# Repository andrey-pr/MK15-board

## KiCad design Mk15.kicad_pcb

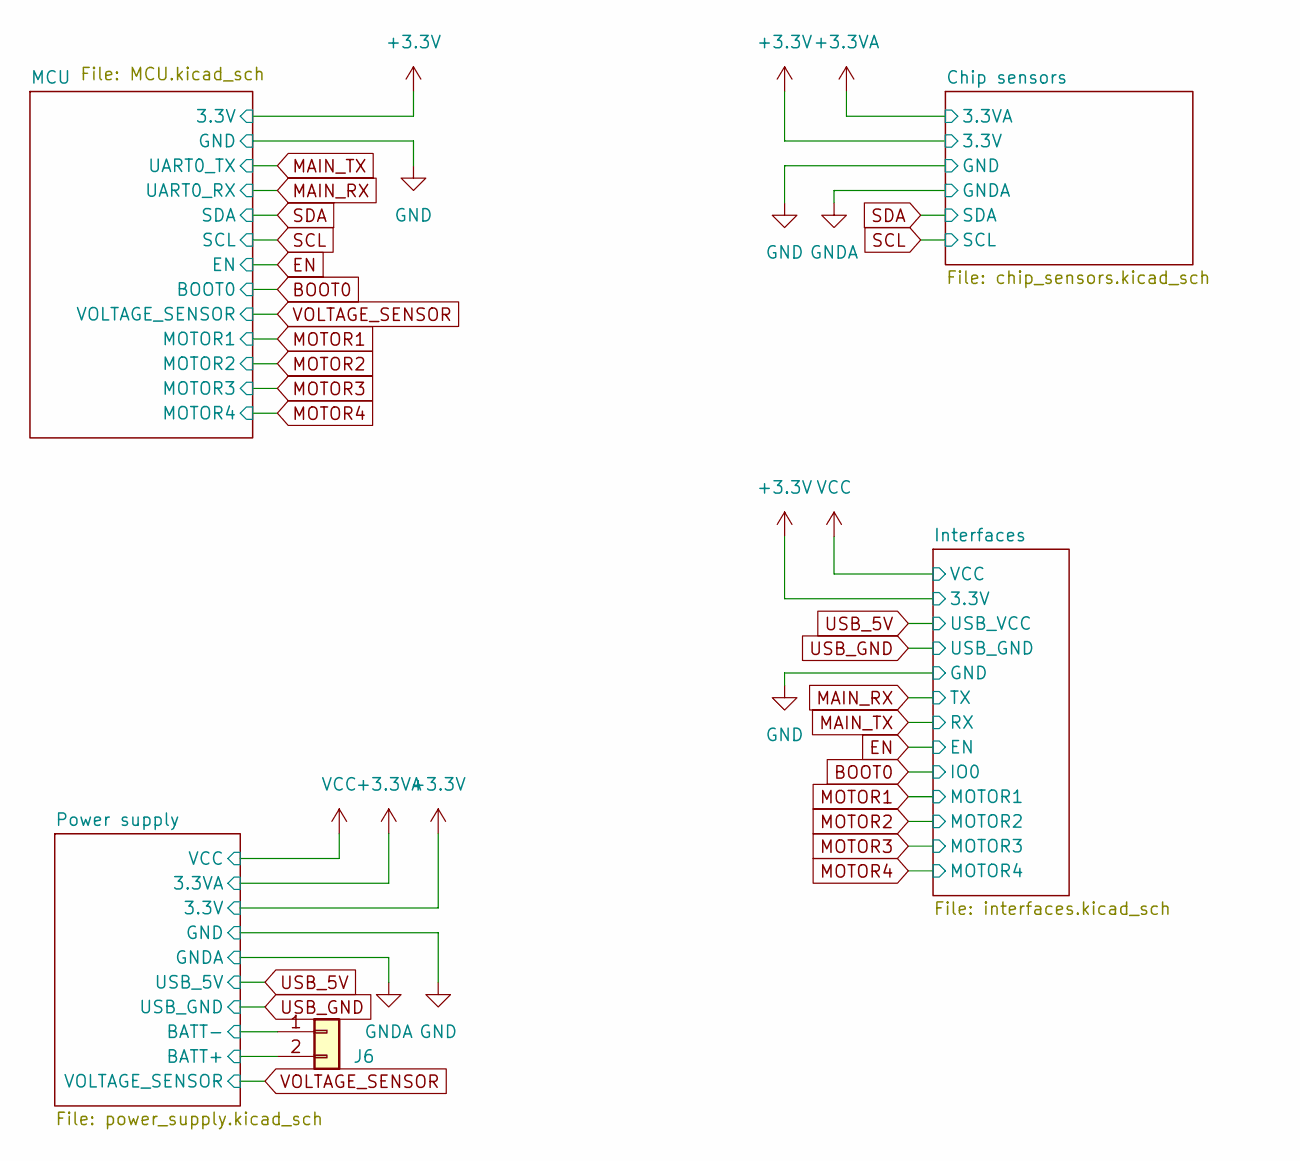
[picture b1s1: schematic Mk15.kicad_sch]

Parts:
J6: Conn_01x02; PinHeader_1x02_P2.54mm_Vertical

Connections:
-BATT: J6.1; also elsewhere on the board
VCC: J6.2; also elsewhere on the board

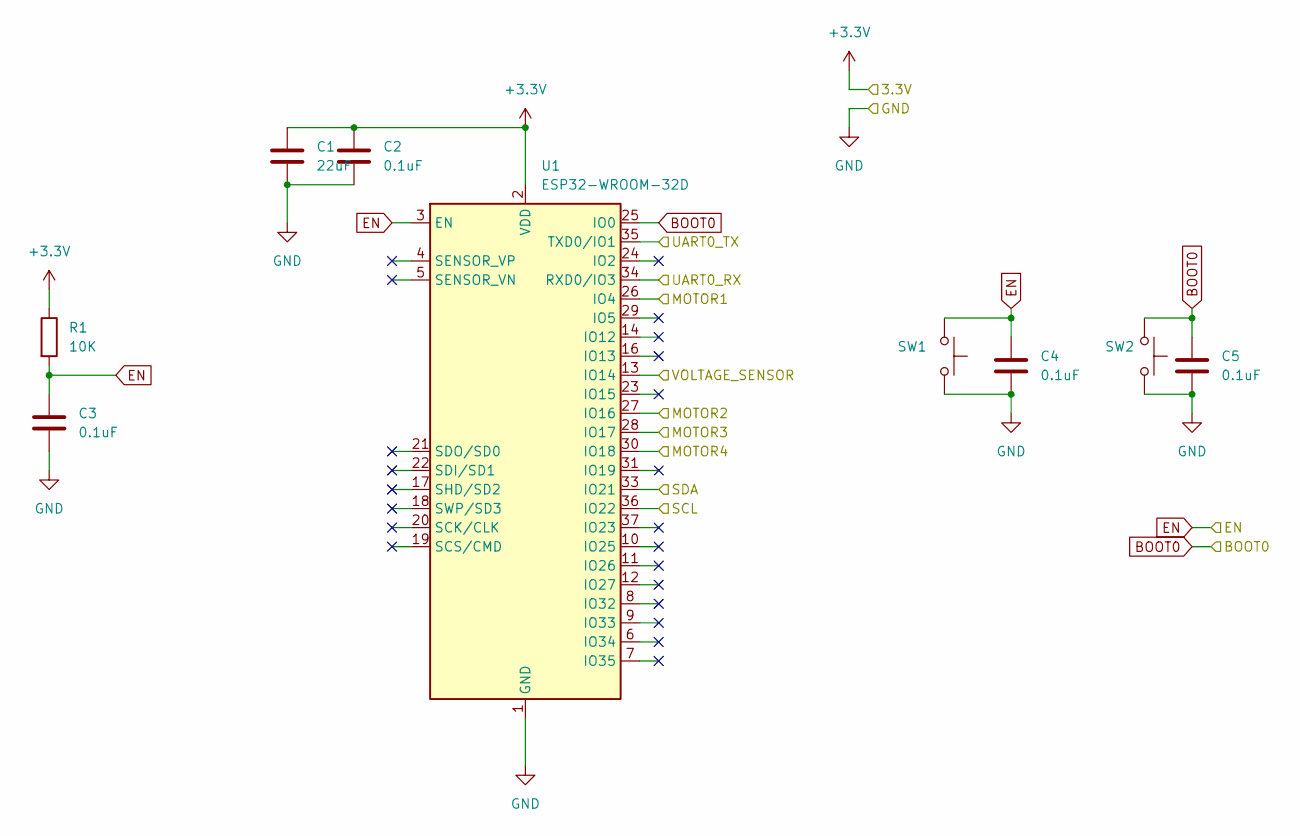
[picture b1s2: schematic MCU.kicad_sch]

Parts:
C1: 22uF; C_0805_2012Metric_Pad1.18x1.45mm_HandSolder
C2, C3, C4, C5: 0.1uF; C_0805_2012Metric_Pad1.18x1.45mm_HandSolder
R1: 10K; R_0805_2012Metric_Pad1.20x1.40mm_HandSolder
SW1, SW2: TS-1101-C-W; SW_SPST_CK_RS282G05A3
U1: ESP32-WROOM-32D; ESP32-WROOM-32

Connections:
+3.3V: C1.1, C2.1, R1.1, U1.2 (VDD); also elsewhere on the board
BOOT0: C5.1, SW2.1, U1.25 (IO0); also elsewhere on the board
EN: C3.1, C4.1, R1.2, SW1.1, U1.3 (EN); also elsewhere on the board
GND: C1.2, C2.2, C3.2, C4.2, C5.2, SW1.2, SW2.2, U1.1 (GND), U1.15 (GND), U1.38 (GND), U1.39 (GND); also elsewhere on the board
MAIN_RX: U1.34 (RXD0/IO3); also elsewhere on the board
MAIN_TX: U1.35 (TXD0/IO1); also elsewhere on the board
MOTOR1: U1.26 (IO4); also elsewhere on the board
MOTOR2: U1.27 (IO16); also elsewhere on the board
MOTOR3: U1.28 (IO17); also elsewhere on the board
MOTOR4: U1.30 (IO18); also elsewhere on the board
SCL: U1.36 (IO22); also elsewhere on the board
SDA: U1.33 (IO21); also elsewhere on the board
VOLTAGE_SENSOR: U1.13 (IO14); also elsewhere on the board

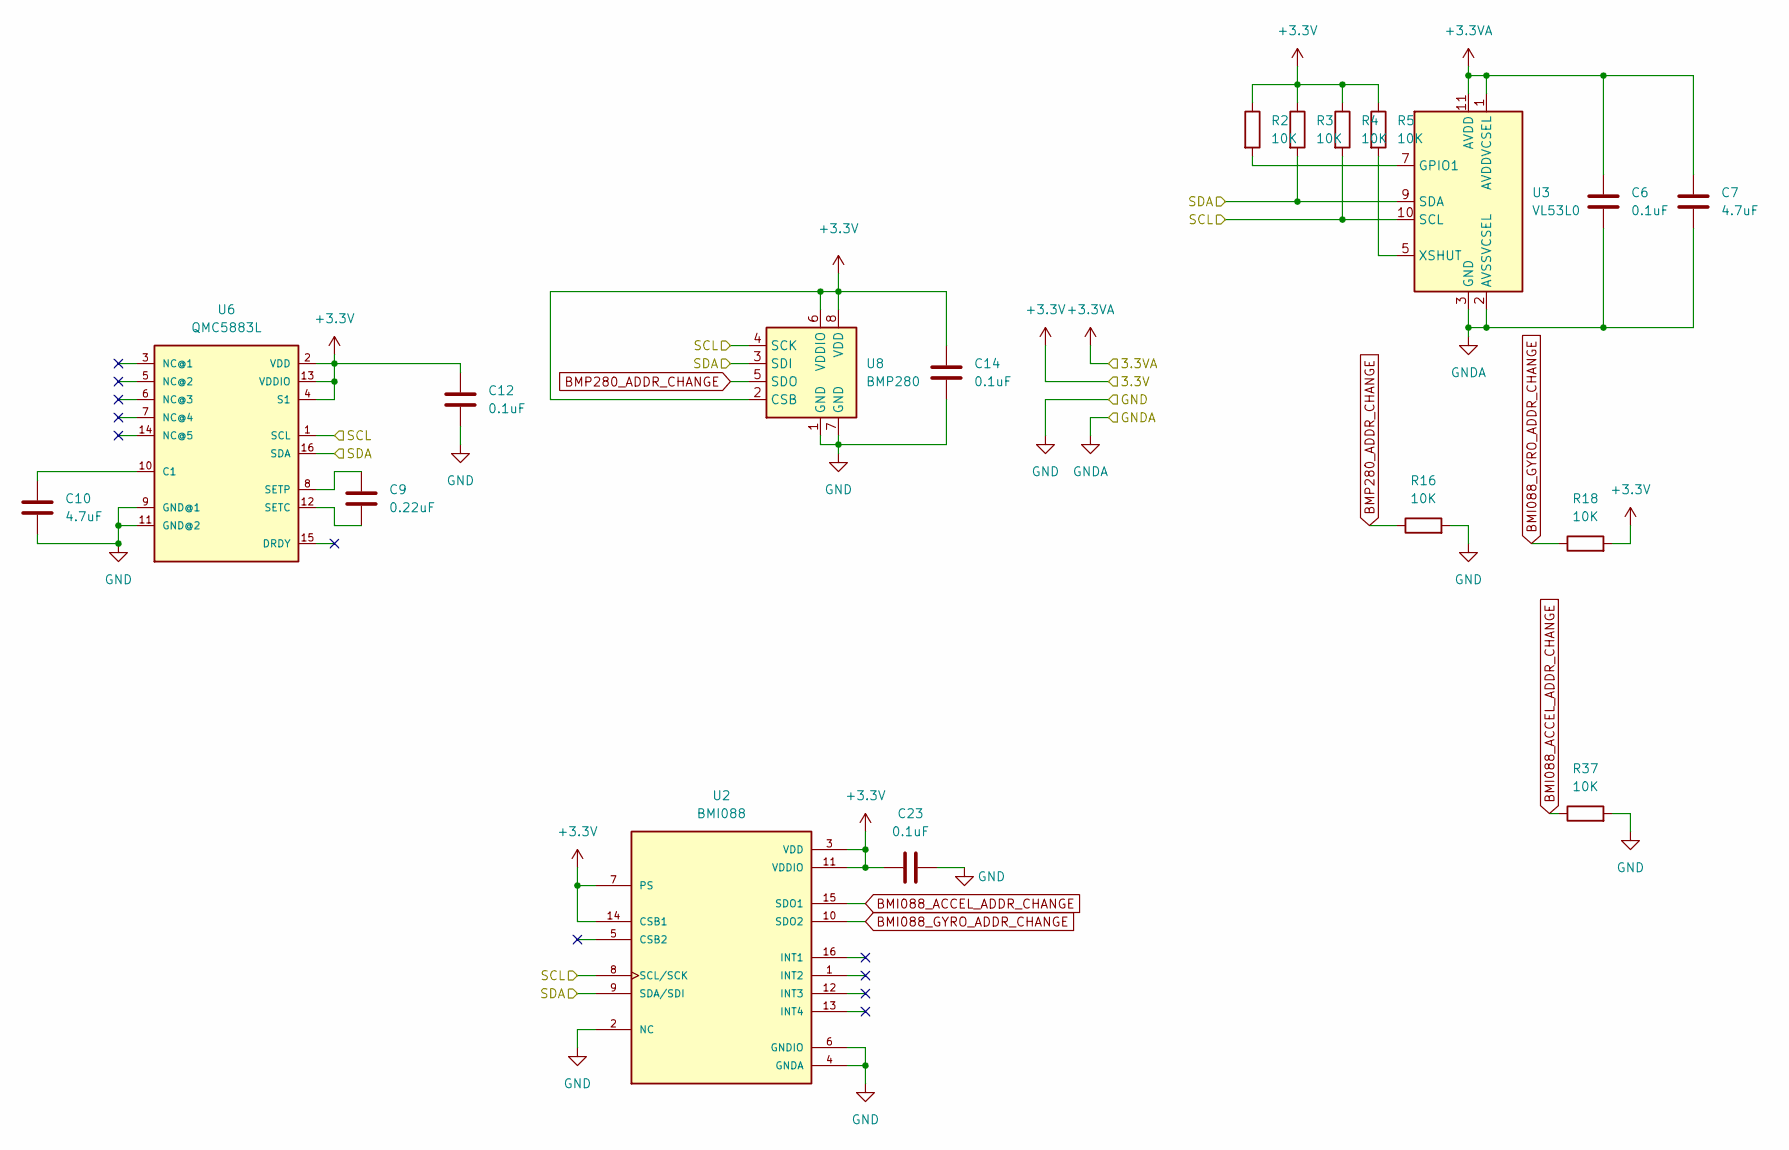
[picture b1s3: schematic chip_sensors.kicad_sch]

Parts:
C6, C12, C14, C23: 0.1uF; C_0805_2012Metric_Pad1.18x1.45mm_HandSolder
C7, C10: 4.7uF; C_0805_2012Metric_Pad1.18x1.45mm_HandSolder
C9: 0.22uF; C_0805_2012Metric_Pad1.18x1.45mm_HandSolder
R2, R3, R4, R5: 10K; R_0603_1608Metric_Pad0.98x0.95mm_HandSolder
R16, R18, R37: 10K; R_0805_2012Metric_Pad1.20x1.40mm_HandSolder
U2: BMI088; PQFN50P450X300X100-16N
U3: VL53L0; ST_VL53L0X
U6: QMC5883L; LPCC-16
U8: BMP280; Bosch_LGA-8_2x2.5mm_P0.65mm_ClockwisePinNumbering

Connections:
+3.3V: C12.1, C14.1, C23.2, R2.1, R3.1, R4.1, R5.1, R18.2, U2.3 (VDD), U2.7 (PS), U2.11 (VDDIO), U2.14 (CSB1), U6.2 (VDD), U6.4 (S1), U6.13 (VDDIO), U8.2 (CSB), U8.6 (VDDIO), U8.8 (VDD); also elsewhere on the board
+3.3VA: C6.1, C7.1, U3.1 (AVDDVCSEL), U3.11 (AVDD); also elsewhere on the board
BMI088_ACCEL_ADDR_CHANGE: R37.1, U2.15 (SDO1)
BMI088_GYRO_ADDR_CHANGE: R18.1, U2.10 (SDO2)
BMP280_ADDR_CHANGE: R16.1, U8.5 (SDO)
GND: C6.2, C7.2, C10.2, C12.2, C14.2, C23.1, R16.2, R37.2, U2.2 (NC), U2.4 (GNDA), U2.6 (GNDIO), U3.2 (AVSSVCSEL), U3.3 (GND), U3.4 (GND), U3.6 (GND), U3.12 (GND), U6.9 (GND@1), U6.11 (GND@2), U8.1 (GND), U8.7 (GND); also elsewhere on the board
unnamed: C9.1, U6.8 (SETP)
unnamed: C9.2, U6.12 (SETC)
unnamed: C10.1, U6.10 (C1)
unnamed: R2.2, U3.7 (GPIO1)
unnamed: R5.2, U3.5 (XSHUT)
SCL: R4.2, U2.8 (SCL/SCK), U3.10 (SCL), U6.1 (SCL), U8.4 (SCK); also elsewhere on the board
SDA: R3.2, U2.9 (SDA/SDI), U3.9 (SDA), U6.16 (SDA), U8.3 (SDI); also elsewhere on the board

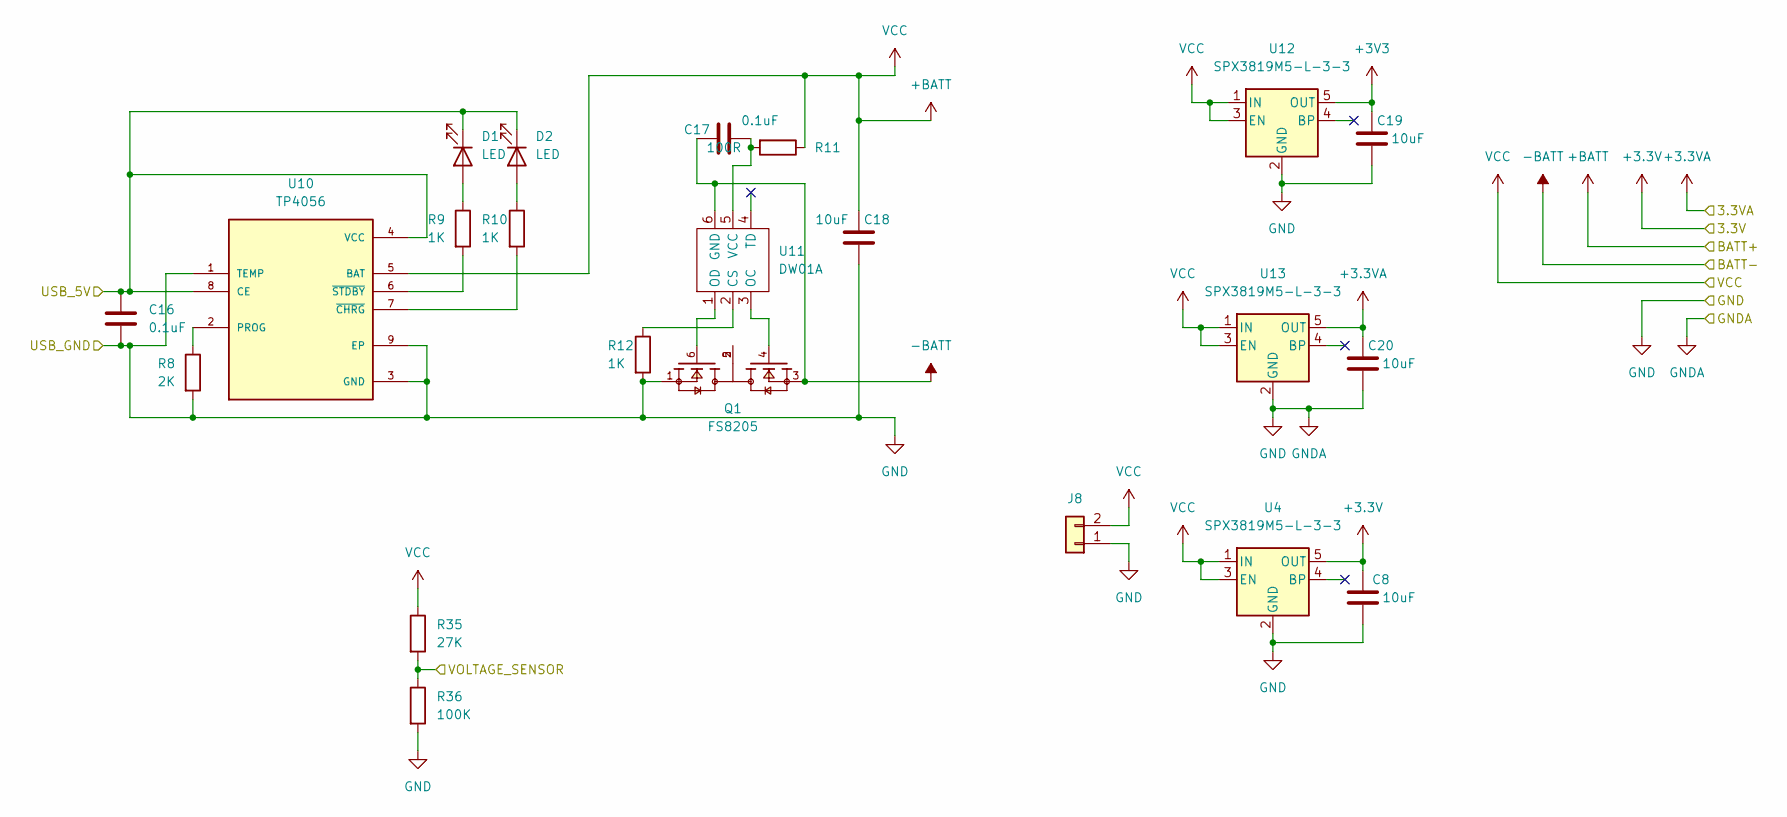
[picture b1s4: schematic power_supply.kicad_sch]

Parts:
C8, C18, C19, C20: 10uF; C_0805_2012Metric_Pad1.18x1.45mm_HandSolder
C16, C17: 0.1uF; C_0805_2012Metric_Pad1.18x1.45mm_HandSolder
D1, D2: LED; LED_0805_2012Metric_Pad1.15x1.40mm_HandSolder
J8: Conn_01x02; PinHeader_1x02_P2.54mm_Vertical
Q1: FS8205; SOT95P280X145-6N; PARTREV 1.9
R8: 2K; R_0805_2012Metric_Pad1.20x1.40mm_HandSolder
R9, R10, R12: 1K; R_0805_2012Metric_Pad1.20x1.40mm_HandSolder
R11: 100R; R_0805_2012Metric_Pad1.20x1.40mm_HandSolder
R35: 27K; R_0805_2012Metric_Pad1.20x1.40mm_HandSolder
R36: 100K; R_0805_2012Metric_Pad1.20x1.40mm_HandSolder
U4, U12, U13: SPX3819M5-L-3-3; SOT-23-5
U10: TP4056; SOP127P600X175-9N
U11: DW01A; SOT-23-6_Handsoldering

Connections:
+3.3V: C8.2, U4.5 (OUT); also elsewhere on the board
+3.3VA: C20.2, U13.5 (OUT); also elsewhere on the board
+3V3: C19.2, U12.5 (OUT); also elsewhere on the board
-BATT: C17.2, Q1.3, U11.6 (GND); also elsewhere on the board
GND: C8.1, C16.2, C18.1, C19.1, C20.1, J8.1, Q1.1, R8.2, R12.2, R36.2, U4.2 (GND), U10.1 (TEMP), U10.3 (GND), U10.9 (EP), U12.2 (GND), U13.2 (GND); also elsewhere on the board
unnamed: C17.1, R11.2, U11.5 (VCC)
unnamed: D1.2 (A), R9.1
unnamed: D2.2 (A), R10.1
unnamed: Q1.2, Q1.5
unnamed: Q1.4, U11.3 (OC)
unnamed: Q1.6, U11.1 (OD)
unnamed: R8.1, U10.2 (PROG)
unnamed: R9.2, U10.6 (~STDBY)
unnamed: R10.2, U10.7 (~CHRG)
unnamed: R12.1, U11.2 (CS)
USB_5V: C16.1, D1.1 (K), D2.1 (K), U10.4 (VCC), U10.8 (CE); also elsewhere on the board
VCC: C18.2, J8.2, R11.1, R35.1, U4.1 (IN), U4.3 (EN), U10.5 (BAT), U12.1 (IN), U12.3 (EN), U13.1 (IN), U13.3 (EN); also elsewhere on the board
VOLTAGE_SENSOR: R35.2, R36.1; also elsewhere on the board

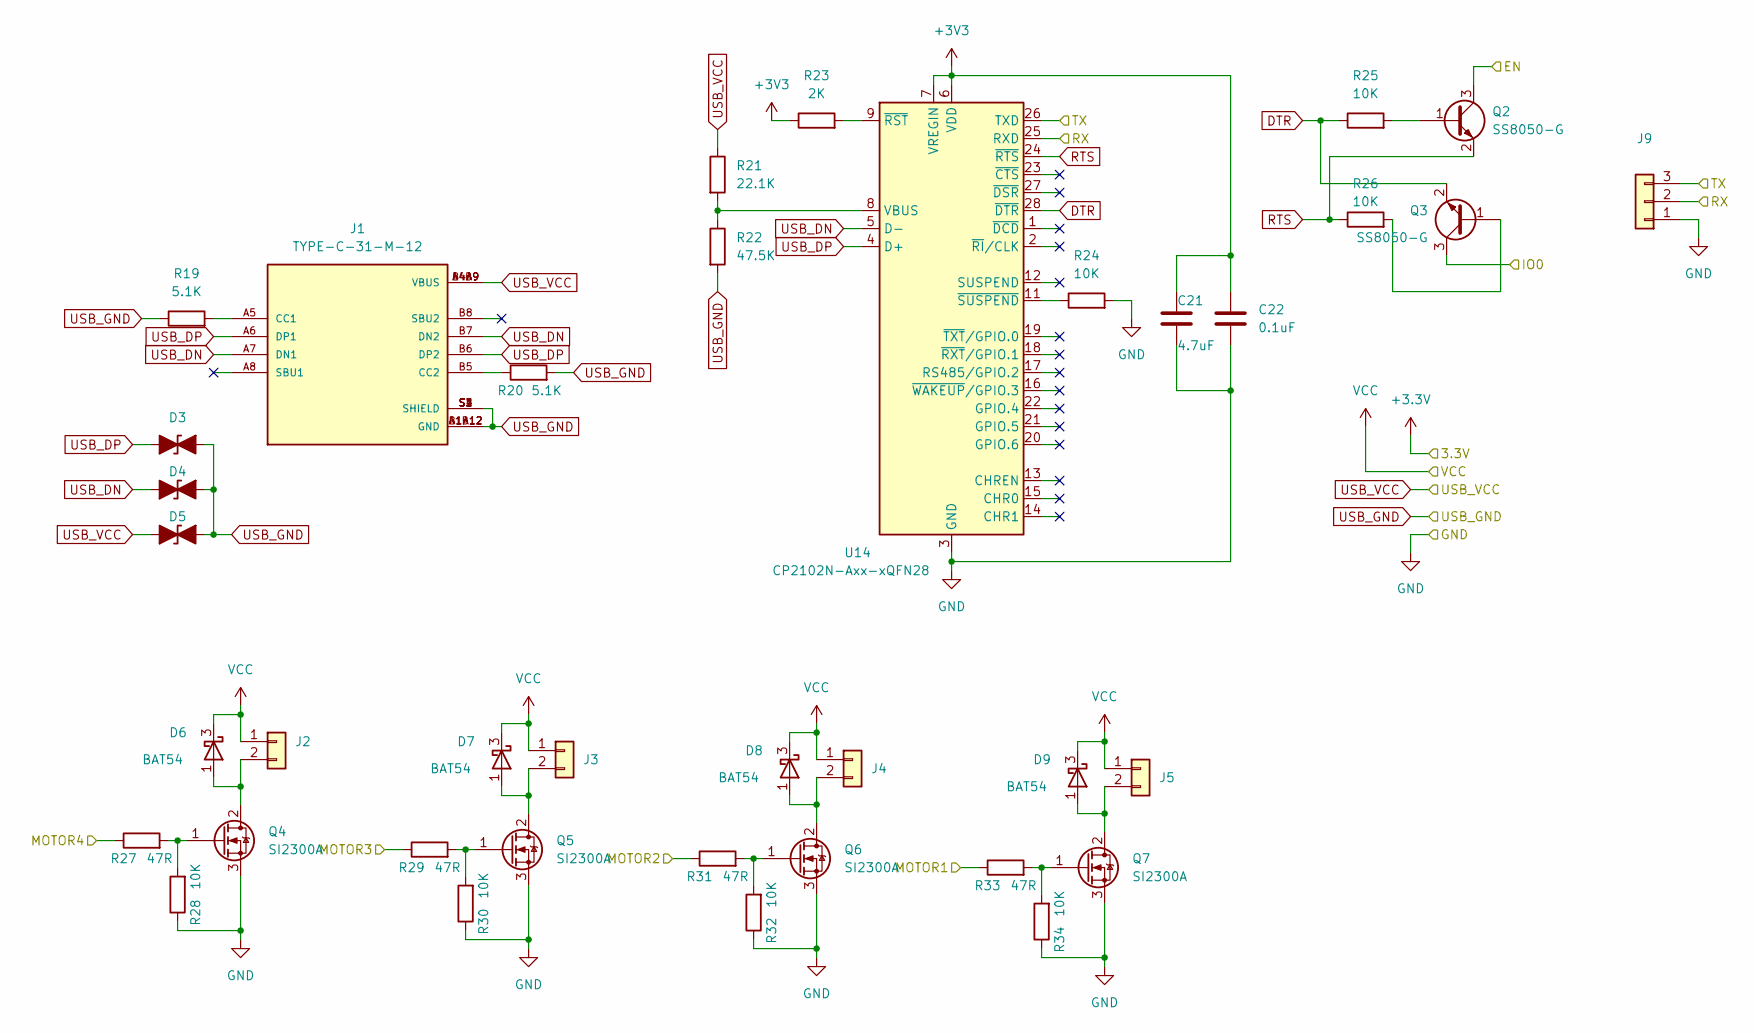
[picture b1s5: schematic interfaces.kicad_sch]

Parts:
C21: 4.7uF; C_0805_2012Metric_Pad1.18x1.45mm_HandSolder
C22: 0.1uF; C_0805_2012Metric_Pad1.18x1.45mm_HandSolder
D3, D4, D5: LRC LESD5D5.0CT1G; D_SOD-523
D6, D7, D8, D9: BAT54; SOT-323_SC-70
J1: TYPE-C-31-M-12; HRO_TYPE-C-31-M-12; PARTREV A
J2, J3, J4, J5: Conn_01x02; PinSocket_1x02_P2.54mm_Vertical
J9: Conn_01x03; PinHeader_1x03_P2.54mm_Vertical
Q2, Q3: SS8050-G; SOT-23
Q4, Q5, Q6, Q7: SI2300A; SOT-23
R19, R20: 5.1K; R_0603_1608Metric_Pad0.98x0.95mm_HandSolder
R21: 22.1K; R_0603_1608Metric_Pad0.98x0.95mm_HandSolder
R22: 47.5K; R_0603_1608Metric_Pad0.98x0.95mm_HandSolder
R23: 2K; R_0603_1608Metric_Pad0.98x0.95mm_HandSolder
R24: 10K; R_0603_1608Metric_Pad0.98x0.95mm_HandSolder
R25, R26, R28, R30, R32, R34: 10K; R_0805_2012Metric_Pad1.20x1.40mm_HandSolder
R27, R29, R31, R33: 47R; R_0805_2012Metric_Pad1.20x1.40mm_HandSolder
U14: CP2102N-Axx-xQFN28; QFN-28-1EP_5x5mm_P0.5mm_EP3.35x3.35mm

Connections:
+3V3: C21.1, C22.1, R23.1, U14.6 (VDD), U14.7 (VREGIN); also elsewhere on the board
BOOT0: Q3.3 (C); also elsewhere on the board
DTR: Q3.2 (E), R25.1, U14.28 (~DTR)
EN: Q2.3 (C); also elsewhere on the board
GND: C21.2, C22.2, D3.2 (A2), D4.2 (A2), D5.2 (A2), J1.A1B12 (GND), J1.B1A12 (GND), J1.S1 (SHIELD), J1.S2 (SHIELD), J1.S3 (SHIELD), J1.S4 (SHIELD), J9.1, Q4.3 (S), Q5.3 (S), Q6.3 (S), Q7.3 (S), R19.1, R20.2, R22.2, R24.2, R28.1, R30.1, R32.1, R34.1, U14.3 (GND), U14.29 (GND); also elsewhere on the board
MAIN_RX: J9.3, U14.26 (TXD); also elsewhere on the board
MAIN_TX: J9.2, U14.25 (RXD); also elsewhere on the board
MOTOR1: R33.1; also elsewhere on the board
MOTOR2: R31.1; also elsewhere on the board
MOTOR3: R29.1; also elsewhere on the board
MOTOR4: R27.1; also elsewhere on the board
unnamed: D6.1 (A), J2.2, Q4.2 (D)
unnamed: D7.1 (A), J3.2, Q5.2 (D)
unnamed: D8.1 (A), J4.2, Q6.2 (D)
unnamed: D9.1 (A), J5.2, Q7.2 (D)
unnamed: J1.A5 (CC1), R19.2
unnamed: J1.B5 (CC2), R20.1
unnamed: Q2.1 (B), R25.2
unnamed: Q3.1 (B), R26.2
unnamed: Q4.1 (G), R27.2, R28.2
unnamed: Q5.1 (G), R29.2, R30.2
unnamed: Q6.1 (G), R31.2, R32.2
unnamed: Q7.1 (G), R33.2, R34.2
unnamed: R21.2, R22.1, U14.8 (VBUS)
unnamed: R23.2, U14.9 (~RST)
unnamed: R24.1, U14.11 (~SUSPEND)
RTS: Q2.2 (E), R26.1, U14.24 (~RTS)
USB_5V: D5.1 (A1), J1.A4B9 (VBUS), J1.B4A9 (VBUS), R21.1; also elsewhere on the board
USB_DN: D4.1 (A1), J1.A7 (DN1), J1.B7 (DN2), U14.5 (D-)
USB_DP: D3.1 (A1), J1.A6 (DP1), J1.B6 (DP2), U14.4 (D+)
VCC: D6.3 (K), D7.3 (K), D8.3 (K), D9.3 (K), J2.1, J3.1, J4.1, J5.1; also elsewhere on the board

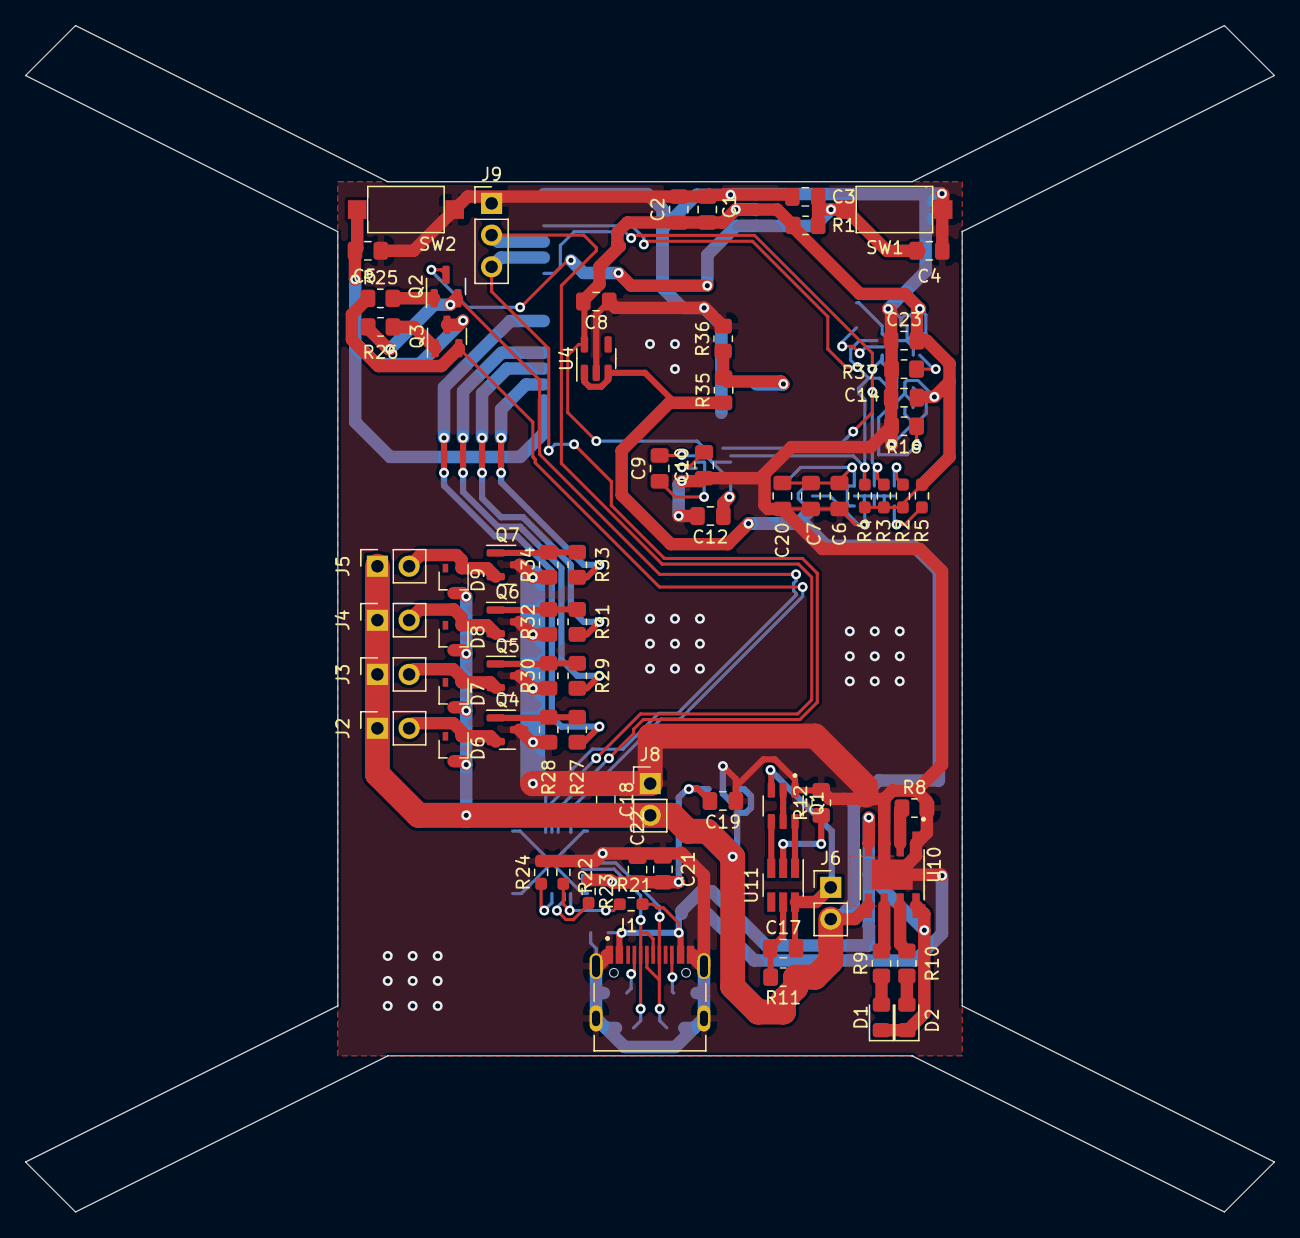
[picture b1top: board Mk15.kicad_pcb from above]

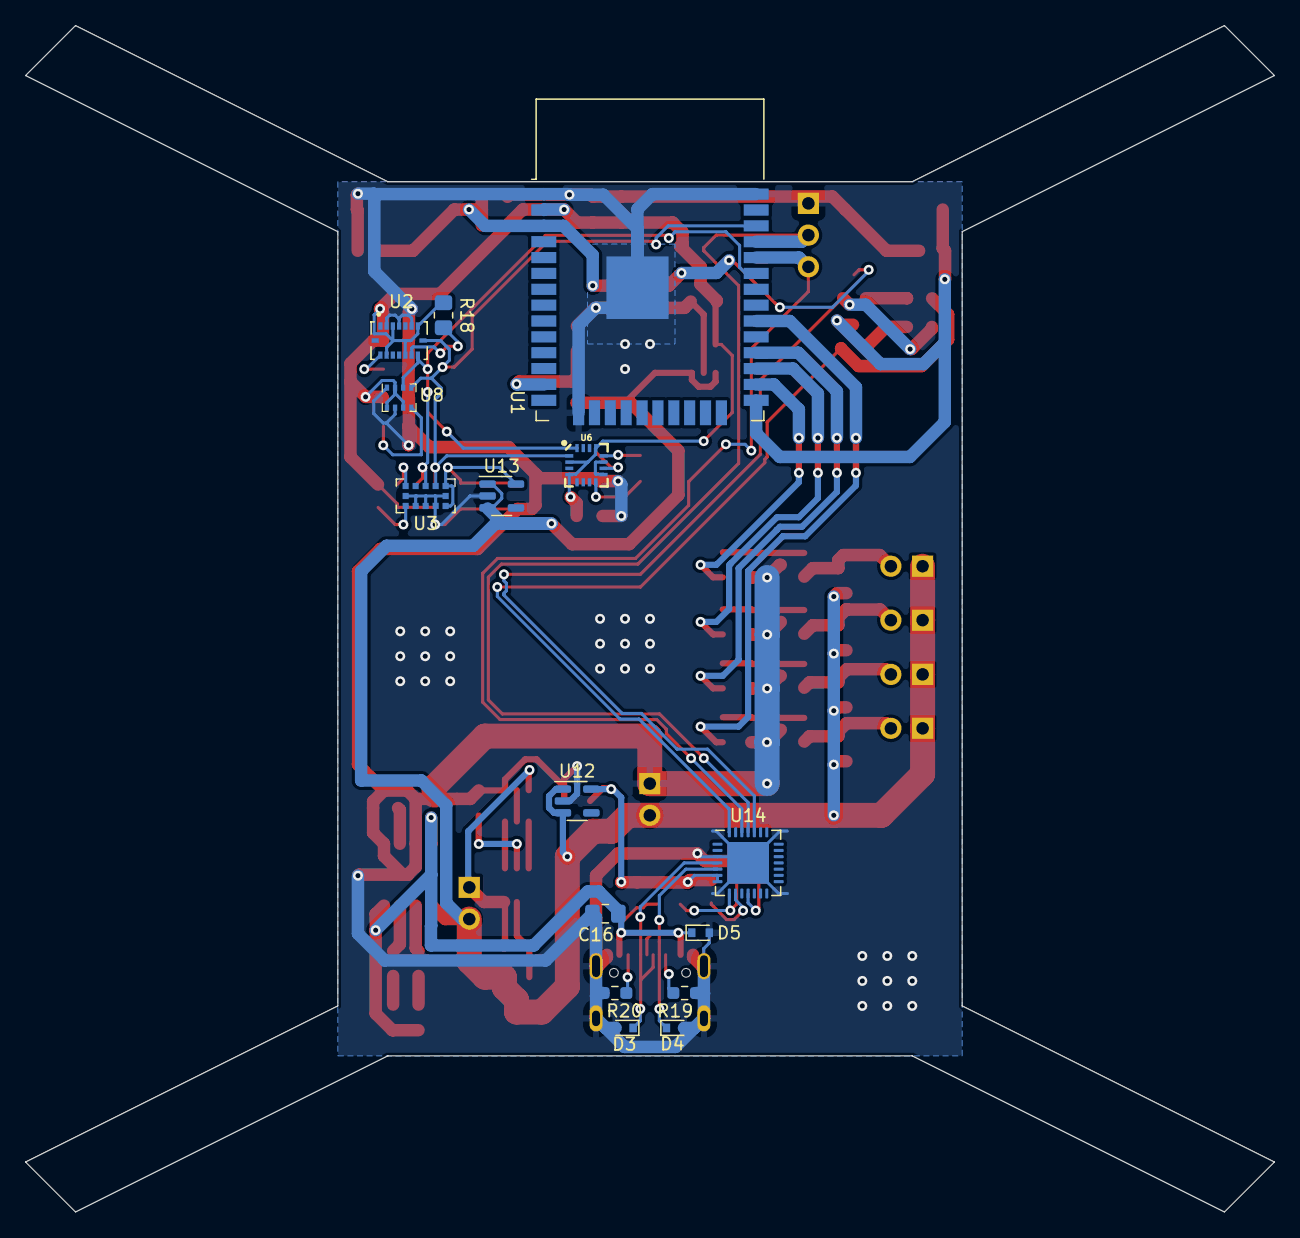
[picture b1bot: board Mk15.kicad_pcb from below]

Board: 2 copper layers, 100.0 x 95.0 mm, 88 parts (15 on the bottom side), 55 nets.

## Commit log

2022-09-04 v1-correction
2022-10-11 board ver1.0
